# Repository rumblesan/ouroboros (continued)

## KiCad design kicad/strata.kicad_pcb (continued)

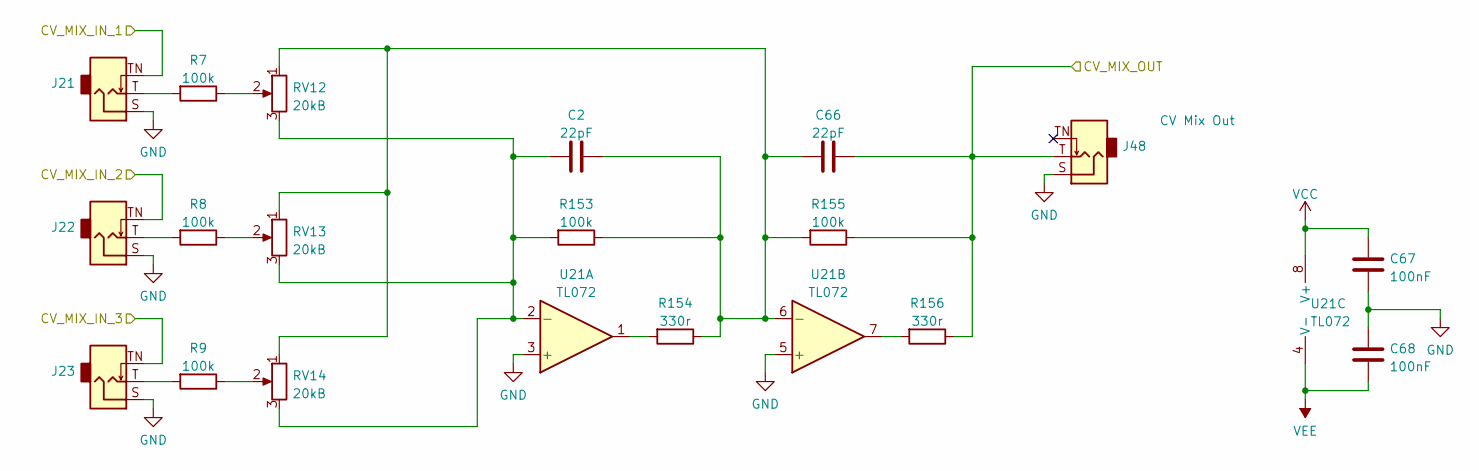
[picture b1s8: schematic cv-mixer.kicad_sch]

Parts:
C2, C66: 22pF; C_Rect_L7.0mm_W2.5mm_P5.00mm; Tolerance 5%
C67, C68: 100nF; C_Rect_L7.0mm_W2.5mm_P5.00mm; Tolerance 5%
J21, J22, J23, J48: Eurorack Mono Jack; Jack_3.5mm_QingPu_WQP-PJ398SM_Vertical; mpn WQP-WQP518MA
R7, R8, R9, R153, R155: 100k; R_Axial_DIN0207_L6.3mm_D2.5mm_P10.16mm_Horizontal; Tolerance 1%
R154, R156: 330r; R_Axial_DIN0207_L6.3mm_D2.5mm_P10.16mm_Horizontal; Tolerance 1%
RV12, RV13, RV14: 20kB; Potentiometer_Alpha_RD901F-40-00D_Single_Vertical
U21: TL072; DIP-8_W7.62mm_Socket

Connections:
/CV Mixer/CV_MIX_IN_1: J21.TN (Tip_normalize); also elsewhere on the board
/CV Mixer/CV_MIX_IN_2: J22.TN (Tip_normalize); also elsewhere on the board
/CV Mixer/CV_MIX_IN_3: J23.TN (Tip_normalize); also elsewhere on the board
/CV Mixer/CV_MIX_OUT: C66.2, J48.T (Tip), R155.1, R156.1; also elsewhere on the board
GND: C67.2, C68.1, J21.S (Sleeve), J22.S (Sleeve), J23.S (Sleeve), J48.S (Sleeve), U21.3 (+), U21.5 (+); also elsewhere on the board
unnamed: C2.1, R153.2, RV12.3, RV13.3, RV14.3, U21.2 (-)
unnamed: C2.2, C66.1, R153.1, R154.1, R155.2, RV12.1, RV13.1, RV14.1, U21.6 (-)
unnamed: J21.T (Tip), R7.2
unnamed: J22.T (Tip), R8.2
unnamed: J23.T (Tip), R9.2
unnamed: R7.1, RV12.2
unnamed: R8.1, RV13.2
unnamed: R9.1, RV14.2
unnamed: R154.2, U21.1
unnamed: R156.2, U21.7
VCC: C67.1, U21.8 (V+); also elsewhere on the board
VEE: C68.2, U21.4 (V-); also elsewhere on the board

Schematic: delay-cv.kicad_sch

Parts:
C60, C61, C62: 10pF; C_Rect_L7.0mm_W2.5mm_P5.00mm; Tolerance 5%
C63: 100pF; C_Rect_L7.0mm_W2.5mm_P5.00mm; Tolerance 5%
C64, C65: 100nF; C_Rect_L7.0mm_W2.5mm_P5.00mm; Tolerance 5%
D37, D38: 1n4148; D_DO-35_SOD27_P7.62mm_Horizontal
Q15, Q16: 2N3904; TO-92_Inline_Wide
R137, R143, R145, R146: 100k; R_Axial_DIN0207_L6.3mm_D2.5mm_P10.16mm_Horizontal; Tolerance 1%
R138: 82k; R_Axial_DIN0207_L6.3mm_D2.5mm_P10.16mm_Horizontal; Tolerance 1%
R139: 10k; R_Axial_DIN0207_L6.3mm_D2.5mm_P10.16mm_Horizontal; Tolerance 1%
R140, R151: 1k; R_Axial_DIN0207_L6.3mm_D2.5mm_P10.16mm_Horizontal; Tolerance 1%
R141, R142: 47k; R_Axial_DIN0207_L6.3mm_D2.5mm_P10.16mm_Horizontal; Tolerance 1%
R144, R147: 220k; R_Axial_DIN0207_L6.3mm_D2.5mm_P10.16mm_Horizontal; Tolerance 1%
R148: 2k2; R_Axial_DIN0207_L6.3mm_D2.5mm_P10.16mm_Horizontal; Tolerance 1%
R149: 22k; R_Axial_DIN0207_L6.3mm_D2.5mm_P10.16mm_Horizontal; Tolerance 1%
R150: 560k; R_Axial_DIN0207_L6.3mm_D2.5mm_P10.16mm_Horizontal; Tolerance 1%
R152: 470; R_Axial_DIN0207_L6.3mm_D2.5mm_P10.16mm_Horizontal; Tolerance 1%
U20: TL074; DIP-14_W7.62mm_Socket

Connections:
/Delay CV/DELAY_CTRL: R152.2; also elsewhere on the board
/Delay CV/TIME: R144.2; also elsewhere on the board
/Delay CV/TIME_CV: R137.1; also elsewhere on the board
/Delay CV/TIME_CV_ATTV_MID: R141.2, R142.1, U20.10 (+); also elsewhere on the board
/Delay CV/TIME_CV_ATTV_TOP: C60.1, R138.2, R139.2, R141.1, R143.1, U20.14; also elsewhere on the board
GND: C64.2, C65.1, Q16.2 (B), R140.2, R142.2, U20.3 (+), U20.5 (+), U20.12 (+); also elsewhere on the board
unnamed: C60.2, D37.1 (K), D38.2 (A), R137.2, R138.1, U20.13 (-)
unnamed: C61.1, R145.2, R146.1, U20.8
unnamed: C61.2, R143.2, R144.1, R145.1, U20.9 (-)
unnamed: C62.1, R149.2, U20.7
unnamed: C62.2, R146.2, R147.1, R148.1, U20.6 (-)
unnamed: C63.1, Q15.3 (C), R150.1, U20.2 (-)
unnamed: C63.2, R151.1, U20.1
unnamed: D37.2 (A), D38.1 (K), R139.1, R140.1
unnamed: Q15.1 (E), Q16.1 (E), R151.2
unnamed: Q15.2 (B), R148.2, R149.1
unnamed: Q16.3 (C), R152.1
VCC: C64.1, R147.2, R150.2, U20.4 (V+); also elsewhere on the board
VEE: C65.2, U20.11 (V-); also elsewhere on the board

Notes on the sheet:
Output voltage range: -0.15v = short delay 0.0 = long delay 0.03 = glitching out
pot CW inverts

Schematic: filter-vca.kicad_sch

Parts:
C31: 1nF; C_Rect_L7.0mm_W3.5mm_P5.00mm; Tolerance 5%
C32, C33: 22pF; C_Rect_L7.0mm_W2.5mm_P5.00mm; Tolerance 5%
C34, C35: 220pF; C_Rect_L7.0mm_W2.5mm_P5.00mm; Tolerance 5%
C36, C37, C38, C39, C41, C42, C43, C44: 100nF; C_Rect_L7.0mm_W2.5mm_P5.00mm; Tolerance 5%
C40: 470nF; C_Rect_L7.0mm_W3.5mm_P5.00mm; Tolerance 5%
D14, D15, D16: 1n4148; D_DO-35_SOD27_P7.62mm_Horizontal
D17, D18: 4v7; D_DO-35_SOD27_P7.62mm_Horizontal
J41: Conn_01x03_Male; PinHeader_1x03_P2.54mm_Vertical
R33: 150k; R_Axial_DIN0207_L6.3mm_D2.5mm_P10.16mm_Horizontal; Tolerance 1%
R34, R35, R36, R37, R39, R44, R48, R50, R52, R54, R57, R60: 100k; R_Axial_DIN0207_L6.3mm_D2.5mm_P10.16mm_Horizontal; Tolerance 1%
R38: 1M5; R_Axial_DIN0207_L6.3mm_D2.5mm_P10.16mm_Horizontal; Tolerance 1%
R40, R51, R58, R64: 22k; R_Axial_DIN0207_L6.3mm_D2.5mm_P10.16mm_Horizontal; Tolerance 1%
R41: 330k; R_Axial_DIN0207_L6.3mm_D2.5mm_P10.16mm_Horizontal; Tolerance 1%
R42: 220k; R_Axial_DIN0207_L6.3mm_D2.5mm_P10.16mm_Horizontal; Tolerance 1%
R43, R53, R59: 330r; R_Axial_DIN0207_L6.3mm_D2.5mm_P10.16mm_Horizontal
R45, R46, R47, R49, R55, R56, R61, R62: 220r; R_Axial_DIN0207_L6.3mm_D2.5mm_P10.16mm_Horizontal; Tolerance 1%
R63: 6k8; R_Axial_DIN0207_L6.3mm_D2.5mm_P10.16mm_Horizontal; Tolerance 1%
U7: TL074; DIP-14_W7.62mm_Socket
U8: TL072; DIP-8_W7.62mm_Socket
U9, U10: LM13700; DIP-16_W7.62mm_Socket

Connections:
/Filter CV/I_FREQ: R51.1, R58.1; also elsewhere on the board
/Filter CV/I_RES: R40.1; also elsewhere on the board
/Filter VCA/AUDIO_INPUT1: R34.2; also elsewhere on the board
/Filter VCA/AUDIO_INPUT2: R35.2; also elsewhere on the board
/Filter VCA/BANDPASS: R53.2; also elsewhere on the board
/Filter VCA/HIGHPASS: R43.2; also elsewhere on the board
/Filter VCA/I_VCA: R63.2; also elsewhere on the board
/Filter VCA/LOWPASS: R59.2; also elsewhere on the board
/Filter VCA/PING: C31.1; also elsewhere on the board
/Filter VCA/VCA_INPUT: C40.1; also elsewhere on the board
/Filter VCA/VCA_OUTPUT: R64.1, U8.1; also elsewhere on the board
GND: C36.2, C37.1, C38.2, C39.1, C41.2, C42.1, C43.2, C44.1, R33.2, R45.1, R46.1, R47.1, R49.1, R55.1, R56.1, R61.1, R62.1, U7.3 (+), U7.5 (+), U7.10 (+), U7.12 (+), U8.3 (+), U8.6 (-); also elsewhere on the board
unnamed: C31.2, D14.2 (A), R33.1
unnamed: C32.1, D14.1 (K), R38.2, R41.2, U8.5 (+)
unnamed: C32.2, D15.2 (A), R38.1, U8.7
unnamed: C33.1, R34.1, R35.1, R36.2, R39.2, R42.1, R48.2, U7.6 (-)
unnamed: C33.2, R39.1, R43.1, R44.2, U7.7
unnamed: C34.1, U7.2 (-), U9.12
unnamed: C34.2, J41.1, R50.2, R52.1, R53.1, R54.2, U7.1
unnamed: C35.1, U7.13 (-), U10.12
unnamed: C35.2, D16.1 (K), R48.1, R57.1, R59.1, U7.14
unnamed: C40.2, R60.2
unnamed: D15.1 (K), R42.2
unnamed: D16.2 (A), R41.1
unnamed: D17.1 (K), D18.1 (K)
unnamed: D17.2 (A), R44.1, R46.2, R52.2, U9.13 (-)
unnamed: D18.2 (A), J41.2
unnamed: R36.1, R37.1, U7.8
unnamed: R37.2, U7.9 (-), U10.5
unnamed: R40.2, U10.1
unnamed: R45.2, U10.3 (+)
unnamed: R47.2, R50.1, U10.4 (-)
unnamed: R49.2, U9.14 (+)
unnamed: R51.2, U9.16
unnamed: R54.1, R55.2, R57.2, U10.13 (-)
unnamed: R56.2, U10.14 (+)
unnamed: R58.2, U10.16
unnamed: R60.1, R61.2, U9.4 (-)
unnamed: R62.2, U9.3 (+)
unnamed: R63.1, U9.1
unnamed: R64.2, U8.2 (-), U9.5
VCC: C36.1, C38.1, C41.1, C43.1, U7.4 (V+), U8.8 (V+), U9.11 (V+), U10.11 (V+); also elsewhere on the board
VEE: C37.2, C39.2, C42.2, C44.2, U7.11 (V-), U8.4 (V-), U9.6 (V-), U10.6 (V-); also elsewhere on the board

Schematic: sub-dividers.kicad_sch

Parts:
C49, C50: 100nF; C_Rect_L7.0mm_W2.5mm_P5.00mm; Tolerance 5%
D20, D21, D22, D23, D24, D25, D26, D27, D28, D29, D30, D31, D32, D33, D34, D35, D36: 1n4148; D_DO-35_SOD27_P7.62mm_Horizontal
Q2, Q3, Q4, Q5, Q6, Q7, Q8: 2N3904; TO-92_Inline_Wide
R85, R87, R90, R91, R92, R97, R98, R101, R104, R107, R110, R113: 100k; R_Axial_DIN0207_L6.3mm_D2.5mm_P10.16mm_Horizontal; Tolerance 1%
R86: 15k; R_Axial_DIN0207_L6.3mm_D2.5mm_P10.16mm_Horizontal; Tolerance 1%
R88, R89: 10k; R_Axial_DIN0207_L6.3mm_D2.5mm_P10.16mm_Horizontal; Tolerance 1%
R93, R99, R102, R105, R108, R111, R114: 1k8; R_Axial_DIN0207_L6.3mm_D2.5mm_P10.16mm_Horizontal; Tolerance 1%
R94, R100, R103, R106, R109, R112, R115: 1k; R_Axial_DIN0207_L6.3mm_D2.5mm_P10.16mm_Horizontal; Tolerance 1%
R95, R96: 4m7; R_Axial_DIN0207_L6.3mm_D2.5mm_P10.16mm_Horizontal; Tolerance 1%
U13: TL072; DIP-8_W7.62mm_Socket
U14, U15, U16, U17: 4017; DIP-16_W7.62mm_Socket

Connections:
/Main Divider/OUT: R88.2; also elsewhere on the board
/Sub Dividers/DIV2: R108.2, R109.1; also elsewhere on the board
/Sub Dividers/DIV3: R99.2, R100.1; also elsewhere on the board
/Sub Dividers/DIV4: R111.2, R112.1; also elsewhere on the board
/Sub Dividers/DIV5: R93.2, R94.1; also elsewhere on the board
/Sub Dividers/DIV6: R102.2, R103.1; also elsewhere on the board
/Sub Dividers/DIV7: R105.2, R106.1; also elsewhere on the board
/Sub Dividers/DIV8: R114.2, R115.1; also elsewhere on the board
/Sub Dividers/RESET: C50.1, R87.1; also elsewhere on the board
/Sub Dividers/TRIG_REF: R85.2, R86.1, U13.2 (-), U13.6 (-)
GND: C49.2, R86.2, R87.2, R90.2, R91.2, R92.2, R94.2, R97.2, R98.2, R100.2, R101.2, R103.2, R104.2, R106.2, R107.2, R109.2, R110.2, R112.2, R113.2, R115.2, U13.4 (V-), U14.8 (VSS), U14.13 (CKEN), U15.8 (VSS), U15.13 (CKEN), U16.8 (VSS), U16.13 (CKEN), U17.8 (VSS), U17.13 (CKEN); also elsewhere on the board
unnamed: C50.2, R89.2
unnamed: D20.1 (K), D21.1 (K), R90.1, U14.15 (Reset)
unnamed: D20.2 (A), D23.2 (A), D27.2 (A), D29.2 (A), R96.1, U13.7
unnamed: D21.2 (A), U14.1 (Q5)
unnamed: D22.1 (K), R97.1, U14.14 (CLK), U15.14 (CLK), U16.14 (CLK), U17.14 (CLK)
unnamed: D22.2 (A), R95.1, U13.1
unnamed: D23.1 (K), D26.1 (K), R98.1, U15.15 (Reset)
unnamed: D24.1 (K), D25.1 (K), Q3.2 (B), R101.1
unnamed: D24.2 (A), U15.7 (Q3)
unnamed: D25.2 (A), Q4.2 (B), U15.3 (Q0)
unnamed: D26.2 (A), U15.5 (Q6)
unnamed: D27.1 (K), D28.1 (K), R104.1, U16.15 (Reset)
unnamed: D28.2 (A), U16.6 (Q7)
unnamed: D29.1 (K), D33.1 (K), R107.1, U17.15 (Reset)
unnamed: D30.1 (K), D31.1 (K), D32.1 (K), D34.1 (K), Q6.2 (B), R110.1
unnamed: D30.2 (A), U17.5 (Q6)
unnamed: D31.2 (A), U17.4 (Q2)
unnamed: D32.2 (A), D35.2 (A), U17.10 (Q4)
unnamed: D33.2 (A), U17.9 (Q8)
unnamed: D34.2 (A), D36.2 (A), Q8.2 (B), U17.3 (Q0)
unnamed: D35.1 (K), D36.1 (K), Q7.2 (B), R113.1
unnamed: Q2.1 (E), R93.1
unnamed: Q2.2 (B), U14.3 (Q0)
unnamed: Q3.1 (E), R99.1
unnamed: Q4.1 (E), R102.1
unnamed: Q5.1 (E), R105.1
unnamed: Q5.2 (B), U16.3 (Q0)
unnamed: Q6.1 (E), R108.1
unnamed: Q7.1 (E), R111.1
unnamed: Q8.1 (E), R114.1
unnamed: R88.1, R91.1, R95.2, U13.3 (+)
unnamed: R89.1, R92.1, R96.2, U13.5 (+)
VCC: C49.1, Q2.3 (C), Q3.3 (C), Q4.3 (C), Q5.3 (C), Q6.3 (C), Q7.3 (C), Q8.3 (C), R85.1, U13.8 (V+), U14.16 (VDD), U15.16 (VDD), U16.16 (VDD), U17.16 (VDD); also elsewhere on the board

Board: 2 copper layers, 376 parts (19 on the bottom side), 261 nets, no tracks yet.

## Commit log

2022-10-10 component positioning mostly done
2022-10-13 initial layout done
2022-10-25 Final changes for rev01
2023-04-30 Updating filter analysis docs
2023-04-30 Adding ibom
2023-04-30 Adding docs to keep track of fixes and changes for rev1
2023-04-30 Full rejig to use attiny for divider
2023-04-30 Unsure what these changes to gerbers are...
2023-04-30 Finished most recent redesign
    probably still needs fixing though
2023-05-01 Layout seems to be all done, though needs further checking
2023-05-13 Updating layout again
2023-05-13 Tweaking VCA circuit
2023-05-13 Adding info about current and power
2023-05-13 deleting fixes list now they're fixed
2023-05-13 deleting changes now they're changed
2023-05-13 Changing name to the mercurial machine
2023-05-13 Updating name in filter analysis
2023-05-13 Updating name in panel files
2023-05-13 geographically reannotate parts
2023-05-13 Updating boms
2023-05-13 Changing name again
2023-05-13 Adding quote to the pcb
2023-05-13 Updating bom and creating part numbers list
2023-05-13 replotting gerbers
2023-05-13 creating schematic pdf
2023-05-13 remaking front panel gerbers
2023-05-13 Add readme
2023-05-14 ignore zip files
2023-05-29 Adding code folder
2023-05-29 Updating for kicad 7
2023-05-29 Adding code comments
2023-05-29 Fixing issues in the divider circuitry
2023-06-25 Minor tweaks to rev2 values
2023-06-25 Removing test points from BOM
2023-06-25 Adding fixes and bugs docs
2023-06-25 Updating zener values
2023-06-25 Updating bom and partnumbers
2023-06-25 Generating new ibom
2023-06-25 Changes after investigations and tweaking
2023-07-20 Changing decoupling caps to ceramic X7R
2023-07-20 Minor tweaks and additional comments
2023-07-20 Regenerating bom
2023-07-25 Updating PCB and rebuilding ibom
2023-07-26 Adding build guide
2023-08-19 Updating diagram
2023-09-10 Initial site creation
2023-09-10 Create CNAME
2023-09-10 Update site with revision info
2023-12-02 Update diagrams
2024-02-08 Adding basic manual docs
2024-09-16 Adding start of analysis for resonance controls
2025-01-10 Updating for new kicad version
2025-01-10 Updating board for new footprint libraries
2025-01-11 Tweaking filter resonance control circuitry
2025-01-11 Tweaking noise circuitry
2025-01-11 Updating pcb after tweaks
2025-07-19 Updating with rev03 changes
2025-07-19 Updating some docs
2025-07-20 Digital ground for divider and other layout improvements
2025-07-20 Switching some opamps
2025-07-20 More layout tweaks
2025-07-20 Updating front panel hole files
